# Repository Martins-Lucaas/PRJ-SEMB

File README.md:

# PRJ-SEMB
Repositório criado para o projeto final da disciplina da SISTEMAS EMBARCADOS da UFU

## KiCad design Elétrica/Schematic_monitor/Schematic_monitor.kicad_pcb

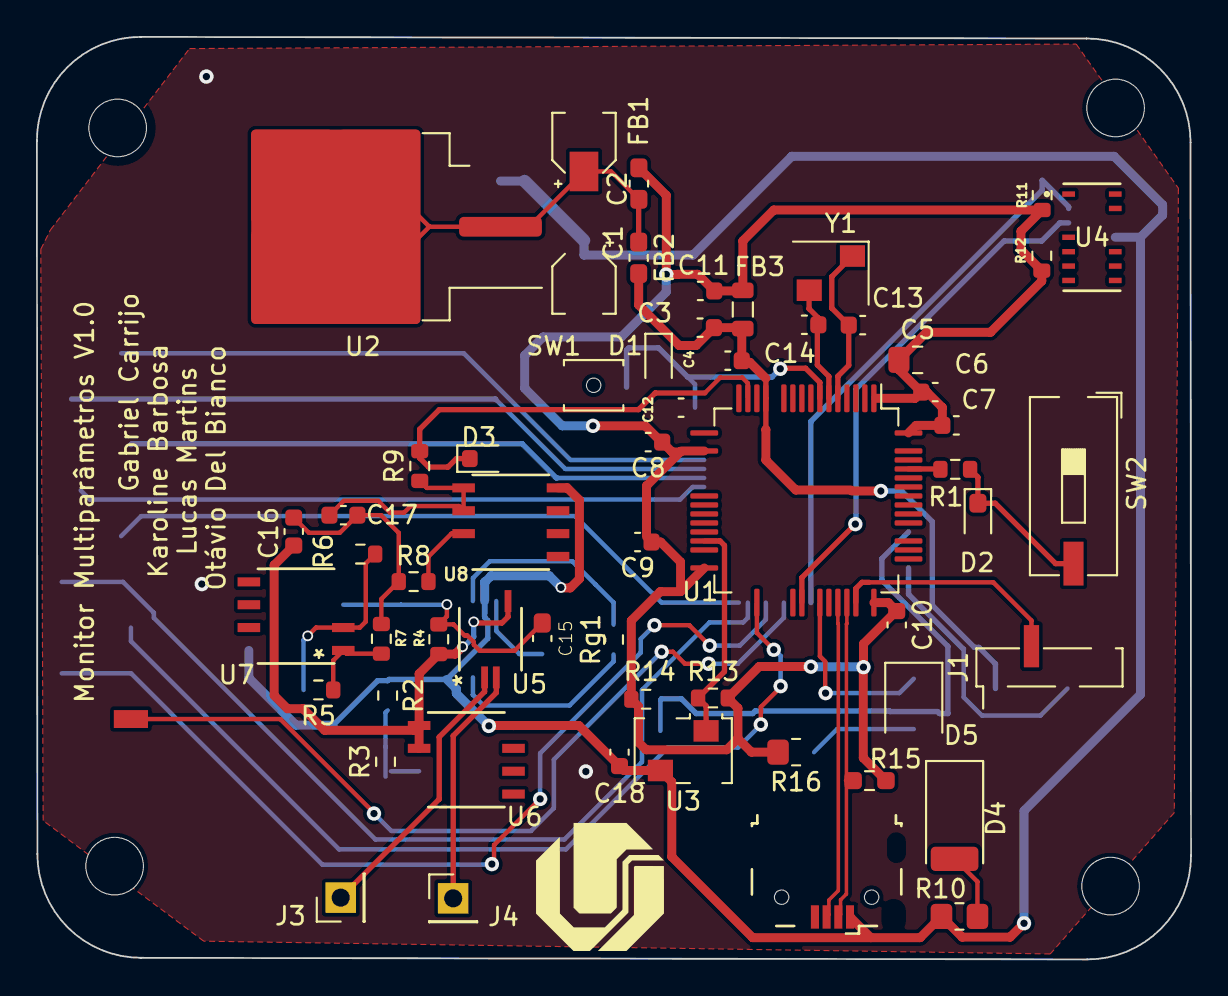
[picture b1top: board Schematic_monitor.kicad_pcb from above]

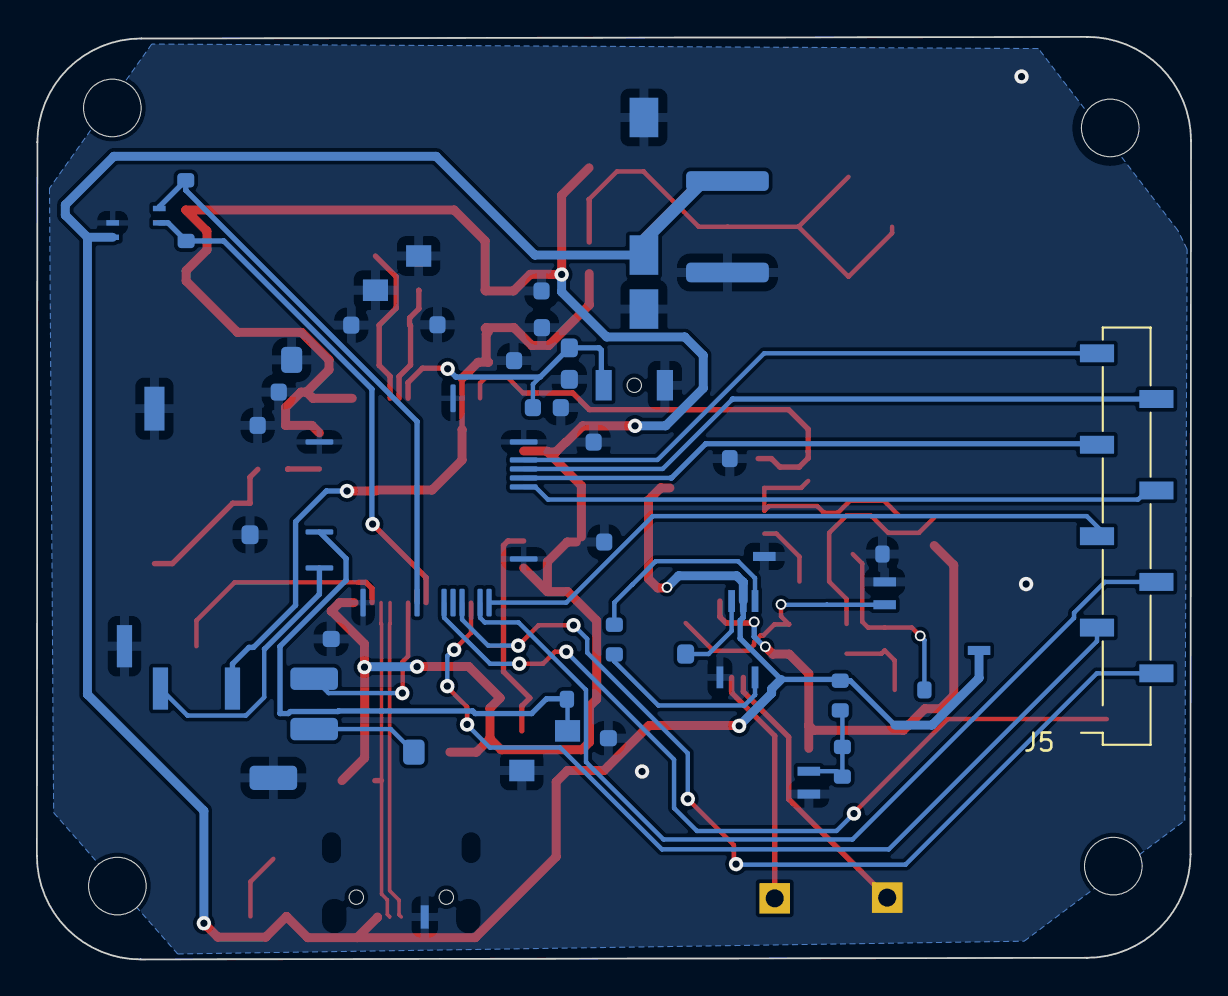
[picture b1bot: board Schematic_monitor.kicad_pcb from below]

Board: 2 copper layers, 64.1 x 51.3 mm, 63 parts (5 on the bottom side), 44 nets.

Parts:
C1, C2: 22uF; CP_Elec_3x5.3
C3: 10nF; C_0603_1608Metric
C4, C11: 1uF; C_0603_1608Metric
C5: 4.7uF; C_0805_2012Metric_Pad1.18x1.45mm_HandSolder
C6, C7, C8, C9, C10, C12: 100nF; C_0603_1608Metric
C13, C14: 26pF; C_0603_1608Metric
C15: 1uF; C_0603_1608Metric_Pad1.08x0.95mm_HandSolder
C16: 330nF; C_0603_1608Metric
C17: 390nF; C_0603_1608Metric
C18: 0.1uF; C_0603_1608Metric
D1, D2: SM6T6V8A; D_0603_1608Metric_Pad1.05x0.95mm_HandSolder
D3: 3.3V; D_0603_1608Metric
D4: LED; LED_2010_5025Metric
D5: LED; LED_1210_3225Metric
FB1: New_Library:FerriteBead; L_0603_1608Metric_Pad1.05x0.95mm_HandSolder
FB2: FerriteBead; L_0603_1608Metric_Pad1.05x0.95mm_HandSolder
FB3: New_Library:FerriteBead; L_0805_2012Metric
H1, H4, H6: MountingHole_Pad; MountingHole_3.2mm_M3
H2: MountingHole_3.2mm_M3
J1: Conn_01x04; PinHeader_1x04_P2.00mm_Vertical_SMD_Pin1Left
J2: USB_B_Micro; USB_Micro-B_Wuerth_629105150521
J3: Eletrode 1; PinHeader_1x01_P2.54mm_Vertical
J4: Eletrode 2; PinHeader_1x01_P2.54mm_Vertical
J5: Conn_01x09; PinSocket_1x09_P2.54mm_Vertical_SMD_Pin1Right
R1, R2, R3, R4: 10k; R_0603_1608Metric
R5: 100k; R_0603_1608Metric
R6: 1K; R_0603_1608Metric
R7, R8, R9: 1k; R_0603_1608Metric
R10: 100; R_0805_2012Metric_Pad1.20x1.40mm_HandSolder
R11, R12: 4.7k; R_0603_1608Metric
R13, R14: 3.5k; R_0603_1608Metric
R15: 1.5K; R_0603_1608Metric_Pad0.98x0.95mm_HandSolder
R16: 1k; R_0805_2012Metric_Pad1.20x1.40mm_HandSolder
Rg1: 6k5; R_0603_1608Metric
SW1: SW_Push; SW_SPST_B3U-1000P-B
SW2: SW_SPDT; SW_DIP_SPSTx01_Slide_9.78x4.72mm_W8.61mm_P2.54mm
U1: STM32F446RET6TR; LQFP-64_10x10mm_P0.5mm
U2: LM1117S-3.3; TO-263-3_TabPin2
U3: MLX90614ESF-ACC-000-TU; Oscillator_SMD_TXC_7C-4Pin_5.0x3.2mm
U4: MAX30100EFD+; 21-0880B_MXM-L
U5: AD623; RM_8_ADI-L
U6, U7, U8: LM358; D8-L
Y1: Crystal_25MHz; Crystal_SMD_SeikoEpson_FA238V-4Pin_3.2x2.5mm

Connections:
+3.3V: C5.1, C6.1, C7.1, C8.1, C9.1, C10.1, C11.1, FB1.2, FB3.1, R11.2, R12.2, R13.2, R14.2, R15.1, R16.2, U1.1 (VBAT), U1.19 (VDD), U1.32 (VDD), U1.48 (VDD), U1.64 (VDD)
+3.3VA: C3.1, C4.1, FB2.2, FB3.2, J1.1, U1.13 (VDDA)
/sw_boot: D2.1 (A1), R1.1, SW2.2 (B)
ADC1-1: D3.1 (K), R9.2, U1.15 (PA1)
BOOT: R1.2, U1.60 (BOOT0)
GND: C1.2, C2.2, C3.2, C4.2, C5.2, C6.2, C7.2, C8.2, C9.2, C10.2, C11.2, C12.2, C13.2, C14.2, C18.1, D1.2 (A2), D2.2 (A2), D3.2 (A), D4.1 (K), J1.4, J2.5 (GND), R6.2, SW1.1, SW2.1 (A), U1.12 (VSSA), U1.18 (VSS), U1.31 (VSS), U1.47 (VSS), U1.63 (VSS), U2.1 (GND), U3.4 (VSS), U4.12 (GND), U5.4 (Vs-), U6.4 (V-), U7.4 (V-), U8.4 (V-), Y1.2, Y1.4
HSE_IN: C13.1, U1.5 (PH0), Y1.1
HSE_OUT: C14.1, U1.6 (PH1), Y1.3
NRST: C12.1, D1.1 (A1), SW1.2, U1.7 (NRST)
unnamed: C15.1, U5.6
unnamed: C16.1, C17.1, R7.2, R8.1
unnamed: D4.2 (A), R10.1
unnamed: D5.2 (A), R16.1
unnamed: J3.1, U5.2 (-)
unnamed: J4.1, U5.3 (+)
unnamed: R5.1, R7.1, U7.1
unnamed: Rg1.1, U5.1 (Rg)
unnamed: Rg1.2, U5.8 (Rg)
unnamed: C2.1, FB1.1, FB2.1, U2.2 (VO)
unnamed: R2.2, R3.1, U6.3 (+)
unnamed: C15.2, R4.1, U7.3 (+)
unnamed: R5.2, R6.1, U7.2 (-)
unnamed: R8.2, U8.3 (+)
unnamed: C17.2, R9.1, U8.1, U8.2 (-)
SWCLK: J1.3, U1.49 (PA14)
SWDIO: J1.2, U1.46 (PA13)
Temp_SCL: R13.1, U1.29 (PB10), U3.1 (SCL/VZ)
Temp_SDA: R14.1, U1.53 (PC12), U3.2 (SDA/PWM)
USB_D+: J2.2 (D-), R15.2, U1.45 (PA12)
USB_D-: J2.3 (D+), U1.44 (PA11)
VBUS: C1.1, C18.2, J2.1 (VBUS), R2.1, R10.2, U2.3 (VI), U3.3 (VDD), U4.11 (VDD), U5.7 (Vs+), U6.8 (V+), U7.8 (V+), U8.8 (V+)
Vref: C16.2, R4.2, U5.5 (Ref), U6.1, U6.2 (-)
displ_cs: J5.5, U1.33 (PB12)
displ_dc: J5.3, U1.35 (PB14)
displ_led: J5.1, U1.38 (PC7)
displ_mosi: J5.6, U1.23 (PA7)
displ_rst: J5.2, U1.36 (PB15)
displ_sck: J5.8, U1.21 (PA5)
led_pin: D5.1 (K), U1.42 (PA9)
oxi_scl: R11.1, U1.41 (PA8), U4.2 (SCL)
oxi_sda: R12.1, U1.40 (PC9), U4.3 (SDA)
touch_cs: J5.4, U1.34 (PB13)
touch_int: J5.9, U1.20 (PA4)
touch_mosi: J5.7, U1.22 (PA6)

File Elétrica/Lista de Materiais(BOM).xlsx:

| Materiais utilizados
 | Quantidade | Dispositivo | Footprint
 | 1 | Amplificador instrumental AD623 | AD623:RM 8 ADI-L
 | 3 | Amplificador operacional LM358 | LM358:D8-L
 | 2 | Capacitor de 22uF (Polarizado) | Capacitor_SMD:CP_Elec_3x5.3
 | 1 | Capacitor de 10nF | Capacitor_SMD:C_0603_1608Metric
 | 2 | Capacitor de 1uF | Capacitor_SMD:C_0603_1608Metric
 | 1 | Capacitor de 4.7uF | Capacitor_SMD:C_0603_1608Metric
 | 6 | Capacitor de 100nF | Capacitor_SMD:C_0805_2012Metric_Pad1.18x1.45mm_HandSolder
 | 2 | Capacitor de 26pF | Capacitor_SMD:C_0603_1608Metric
 | 1 | Capacitor de 1uF | Capacitor_SMD:C_0603_1608Metric_Pad1.08x0.95mm_HandSolder
 | 1 | Capacitor de 330nF | Capacitor_SMD:C_0603_1608Metric
 | 1 | Capacitor de 390nF | Capacitor_SMD:C_0603_1608Metric
 | 1 | Capacitor de 0.1uF | Capacitor_SMD:C_0603_1608Metric
 | 1 | Cristal oscilador de 25Mhz | Crystal:Crystal_SMD_SeikoEpson_FA238V-4Pin_3.2x2.5mm
 | 1 | Conector 01x09 | Connector_PinSocket_2.54mm:PinSocket_1x09_P2.54mm_Vertical_SMD_Pink_Right
 | 1 | Conector 01x04 | Connector_PinHeader_2.00mm:PinHeader_1x04_P2.00mm_Vertical_SMD_Pink_Left
 | 2 | Diodo SM6T6V8A | Diode_SMD:D_0603_l608Metric_Padl.05x0.95mm_HandSolder
 | 1 | Diodo Zener de 3.3V | Diode_SMD:D_0603_l608Metric
 | 1 | Display ILI9488 | LCD_device:_ILI9488
 | 2 | Eletrodo 1x01 P2.54M vertical | Connector_PinHeader_2.54mm:PinHeader_lx01_P2.54mm_Vertical
 | 2 | LED | LED_SMD:LED_2010_5025Metric
 | 7 | Mounting Hole Pad de 2.2mm | MountingHole:MountingHole 2.2mm_M2_DIN965_Pad
 | 3 | Núcleo de Ferrita | Inductor_SMD:L_0603 l608Metric_Pad1.05x0.95mm_HandSolder
 | 1 | Regulador de tensão LM1117S-3.3 | Package_TO_SOT_SMD:TO-263-3_TabPin2
 | 4 | Resistor de 10k Ω | Resistor_SMD:R_0603_l608Metric
 | 1 | Resistor de 100k Ω | Resistor_SMD:R_0603_l608Metric
 | 5 | Resistor de 1k Ω | Resistor_SMD:R_0603_l608Metric
 | 1 | Resistor de 10k Ω | Resistor_SMD:R_0603_l608Metric
 | 1 | Resistor de 100 Ω | Resistor_SMD:R_0603_l608Metric_Pad1.20x1.40mm_HandSolder
 | 1 | Resistor de 6.5k Ω | Resistor_SMD:R_0603_l608Metric
 | 1 | Sensor de temperatura MLX90614ESF-ACC-000-TU | temp:MLX906l4xCC_MEL
 | 1 | Sensor de oximetria MAX30100EFD+ | oximeter:21-0880B_MXM-L
 | 1 | STM32F446RET6TR | Package_QFP:LQFP-64_10x10mm_P0.5mm
 | 1 | Switch button push | Button_Switch_SMD:SW_SPST_B3U-1000P-B
 | 1 | Switch button SPDT | Button_Switch_SMD:SW_DIP_SPSTx0l_Slide_9.78x4.72mm_W8.61mm_P2.54mm
 | 1 | USB B Micro | Connector_USB:USB_Micro-B_Wuerth_629105150521

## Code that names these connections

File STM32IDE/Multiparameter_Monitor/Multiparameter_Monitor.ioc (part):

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Mcu.Name=STM32F446R(C-E)Tx
Mcu.Package=LQFP64
Mcu.UserName=STM32F446RETx
PA1.GPIOParameters=GPIO_PuPd,GPIO_Mode
PA1.GPIO_Mode=GPIO_MODE_ANALOG
PA1.GPIO_PuPd=GPIO_NOPULL
PA1.Signal=ADCx_IN1
PA10.Signal=GPIO_Output
PA11.Mode=Device_Only
PA11.Signal=USB_OTG_FS_DM
PA12.Mode=Device_Only
PA12.Signal=USB_OTG_FS_DP
PA13.Mode=Serial_Wire
PA13.Signal=SYS_JTMS-SWDIO
PA14.Mode=Serial_Wire
PA14.Signal=SYS_JTCK-SWCLK
PA4.GPIOParameters=GPIO_PuPd,GPIO_Label,GPIO_ModeDefaultEXTI
PA4.GPIO_Label=TOUCH_INT
PA4.GPIO_ModeDefaultEXTI=GPIO_MODE_IT_FALLING
PA4.GPIO_PuPd=GPIO_PULLUP
PA4.Signal=GPXTI4
PA5.GPIOParameters=GPIO_Label
PA5.GPIO_Label=DISPL_SCK
PA5.Mode=Full_Duplex_Master
PA5.Signal=SPI1_SCK
PA6.GPIOParameters=GPIO_Label
PA6.GPIO_Label=TOUCH_MISO
PA6.Mode=Full_Duplex_Master
PA6.Signal=SPI1_MISO
PA7.GPIOParameters=GPIO_Label
PA7.GPIO_Label=DISPL_MOSI
PA7.Mode=Full_Duplex_Master
PA7.Signal=SPI1_MOSI
PA8.GPIOParameters=GPIO_Label
PA8.GPIO_Label=oxi_scl
PA8.Mode=I2C
PA8.Signal=I2C3_SCL
PA9.GPIOParameters=GPIO_Label
PA9.GPIO_Label=led_adc
PA9.Signal=GPIO_Output
PB10.GPIOParameters=GPIO_Label
PB10.GPIO_Label=temp_scl
PB10.Mode=I2C
PB10.Signal=I2C2_SCL
PB12.GPIOParameters=GPIO_Speed,PinState,GPIO_Label
PB12.GPIO_Label=DISPL_CS
PB12.GPIO_Speed=GPIO_SPEED_FREQ_HIGH
PB12.PinState=GPIO_PIN_SET
PB12.Signal=GPIO_Output
PB13.GPIOParameters=GPIO_Speed,PinState,GPIO_Label
PB13.GPIO_Label=TOUCH_CS
PB13.GPIO_Speed=GPIO_SPEED_FREQ_HIGH
PB13.PinState=GPIO_PIN_SET
PB13.Signal=GPIO_Output
PB14.GPIOParameters=GPIO_Speed,PinState,GPIO_Label
PB14.GPIO_Label=DISPL_DC
PB14.GPIO_Speed=GPIO_SPEED_FREQ_HIGH
PB14.PinState=GPIO_PIN_SET
PB14.Signal=GPIO_Output
PB15.GPIOParameters=GPIO_Label
PB15.GPIO_Label=DISPL_RST
PB15.Signal=GPIO_Output
PC10.GPIOParameters=GPIO_Label
PC10.GPIO_Label=usart_emg_tx
PC10.Mode=Asynchronous
PC10.Signal=USART3_TX
PC12.GPIOParameters=GPIO_Label
PC12.GPIO_Label=temp_sda
PC12.Mode=I2C
PC12.Signal=I2C2_SDA
PC5.GPIOParameters=GPIO_Label
PC5.GPIO_Label=usart_emg_rx
PC5.Mode=Asynchronous
PC5.Signal=USART3_RX
PC7.GPIOParameters=GPIO_Label
PC7.GPIO_Label=DISPL_LED
PC7.Signal=S_TIM3_CH2
PC9.GPIOParameters=GPIO_Label
PC9.GPIO_Label=oxi_sda
PC9.Mode=I2C
PC9.Signal=I2C3_SDA
PH0-OSC_IN.Mode=HSE-External-Oscillator
PH0-OSC_IN.Signal=RCC_OSC_IN
PH1-OSC_OUT.Mode=HSE-External-Oscillator
PH1-OSC_OUT.Signal=RCC_OSC_OUT
RCC.HSE_VALUE=25000000
RCC.SYSCLKFreq_VALUE=120000000
RCC.SYSCLKSource=RCC_SYSCLKSOURCE_PLLRCLK
board=custom

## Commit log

2023-09-22 Create datasheets
2023-09-22 Adicionar tcc
2023-09-22 Componentes inciais + Diagrama de blocos
2023-09-24 Adicionando ultimos ar
2023-10-24 Atualizções
2023-10-29 Mudanças no kicad e no Código base da STM
2023-10-29 teste
2023-10-29 KICAD
    Esquemático da placa do monitor
2023-10-29 Correção Geral das pastas
    Concertei diretório das pastas
2023-10-29 Changes in STM32Code
    Add new functions for I2C communications
2023-10-30 Temp sensor
    Adicionado sensor de temperatura
2023-10-30 sensor de temperatura
2023-10-30 troquei o nome do i2c oxi
2023-10-30 Monitor_Main changes
    Inicio das funções do monitor multiparametros
2023-10-30 kicad labels
2023-10-30 Deleted files
2023-10-30 Organização
2023-10-30 Atualizações
2023-10-31 Versão PRJ2 e PRJ3 quase finalizada
    Poucos detalhes precisam ser alterados para o envio dos trabalhos pelo menos do PRJ2. PRJ3 está finalizado
2023-10-31 Final Detalis to PRJ2
    Added final detalis in PCB desing and STM32 configuration.
2023-10-31 revisao prj2 prj3
2023-10-31 Mudanças kicad
2023-10-31 Ajustes
2023-11-02 Entrega PRJ2 PRJ3
2023-11-02 PRJ2 correções
2023-11-03 Correções
2023-11-04 Inicio PRJ4
2023-11-05 PRJ4
2023-11-07 Inicio PRJ5
2023-11-07 PJR5
2023-11-14 PRJ5
2023-11-19 Alterações PRJ4
2023-11-20 PRJ4 envio
2023-11-20 PRJ4 details
2023-11-20 PRJ4 final
2023-11-22 Multiparameter Monitor PCB
2023-11-22 prj5-sensor_temp
2023-11-22 Fix PRJ5
2023-11-23 PRJ5 - fix makefile
2023-11-23 PRJ5-F Fix makefile
2023-11-23 prj4 - final
2023-11-23 Criado source e header files
2023-11-23 test
2023-11-24 final
2023-11-25 Sensor de Oximetria
    Adicionado os códigos .c e .h do sensor MX30102
2023-11-25 Fix debug
2023-11-26 PRJ4 - Entregue
2023-11-27 Atualização sensor MAX30100
    códigos .c e .h do sensor max30100 atualizados
2023-11-27 Comentários - MLX90614
2023-11-27 Mudanças PRJ5 e PRJ4
2023-11-27 Comentários
2023-11-27 teste_display
2023-11-28 teste_display2
2023-11-28 Fix all project
2023-11-28 Finalizado EMG_ADC
2023-11-28 Prj5 Aguardando display config
2023-11-28 Entrega PRJ4
2023-11-28 EMG finalizado
2023-11-28 Prj5 _ main
2023-11-28 Build Estável
2023-11-28 Display_fixed
2023-11-28 PRJ5 - Entrega
2023-11-28 Final commit
